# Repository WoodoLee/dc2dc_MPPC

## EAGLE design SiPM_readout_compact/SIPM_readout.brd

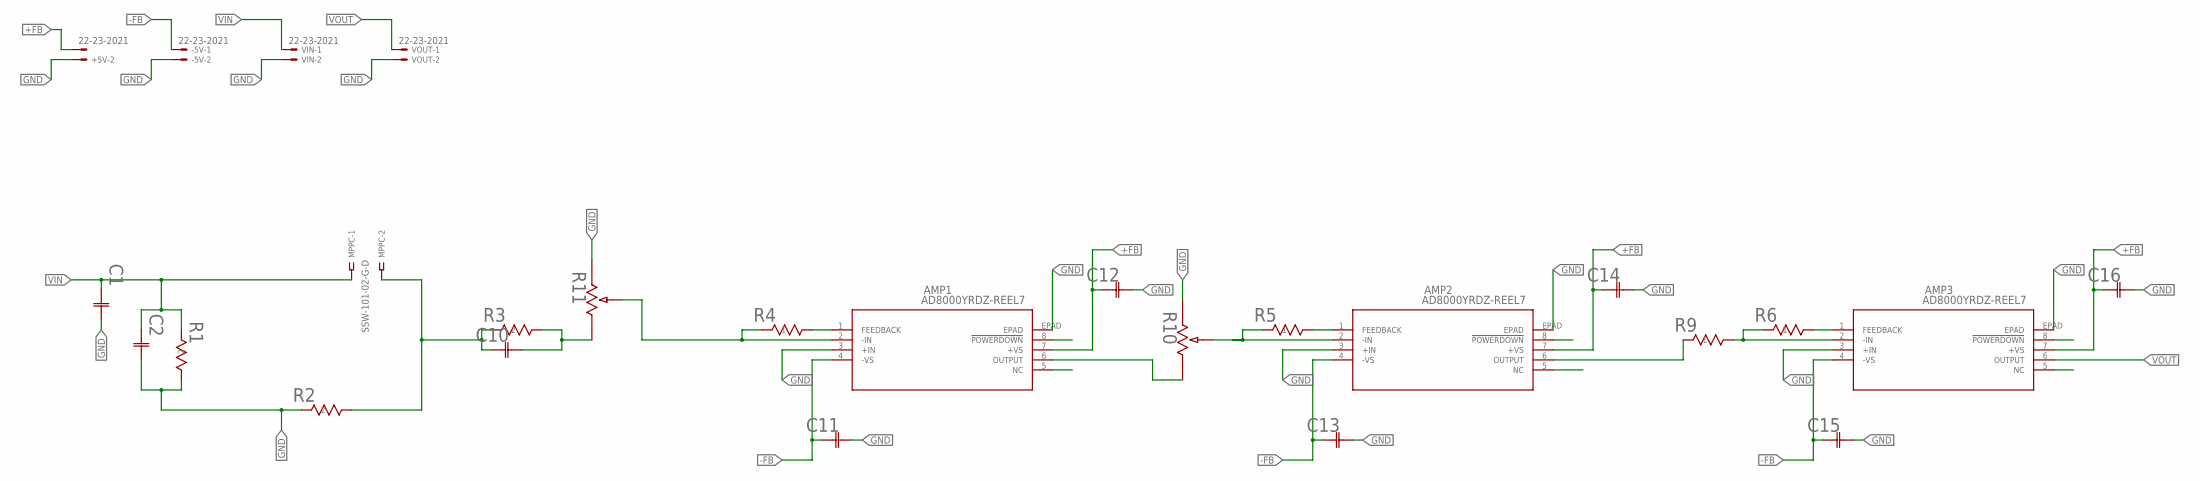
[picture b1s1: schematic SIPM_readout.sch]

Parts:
+5V: 22-23-2021
-5V: 22-23-2021
AMP1, AMP2, AMP3: AD8000YRDZ-REEL7; RD_8_1_ADI
C1: C3225X7S2A335M200ABCAP_3225_TDK-M; CAP_3225_TDK-M
C2: C3225X7R2A105K200AACAP_3225_TDK-M; CAP_3225_TDK-M
C10: CGA3E2C0G1H101J080AA; CAP_1608_TDK
C11, C12, C13, C14, C15, C16: CL10B104KB8NNNL; CAP_CL10_SAM
MPPC: SSW-101-02-G-D
R1: RC0603FR-072ML; RC0603N_YAG
R2, R3: RT0603BRD0710RL; RC0603N_YAG
R4, R5, R6, R9: ESR03EZPF1001; RES_R0603_ROM
R10, R11: 3214W-1-103E; POT_3214W
VIN: 22-23-2021
VOUT: 22-23-2021

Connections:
+FB: +5V.1, AMP1.7 (+VS), AMP2.7 (+VS), AMP3.7 (+VS), C12.1, C14.1, C16.1
-FB: -5V.1, AMP1.4 (-VS), AMP2.4 (-VS), AMP3.4 (-VS), C11.1, C13.1, C15.1
GND: +5V.2, -5V.2, AMP1.3 (+IN), AMP1.EPAD, AMP2.3 (+IN), AMP2.EPAD, AMP3.3 (+IN), AMP3.EPAD, C1.2, C2.2, C11.2, C12.2, C13.2, C14.2, C15.2, C16.2, R1.1, R2.2, R10.1, R11.1, VIN.2, VOUT.2
unnamed: AMP1.6 (OUTPUT), R10.3
unnamed: C10.1, MPPC.2, R2.1, R3.2
unnamed: C10.2, R3.1, R11.3
unnamed: AMP1.2 (-IN), R4.1, R11.2
unnamed: AMP1.1 (FEEDBACK), R4.2
unnamed: AMP2.1 (FEEDBACK), R5.2
unnamed: AMP2.2 (-IN), R5.1, R10.2
unnamed: AMP3.1 (FEEDBACK), R6.2
unnamed: AMP3.2 (-IN), R6.1, R9.2
unnamed: AMP2.6 (OUTPUT), R9.1
VIN: C1.1, C2.1, MPPC.1, R1.2, VIN.1
VOUT: AMP3.6 (OUTPUT), VOUT.1

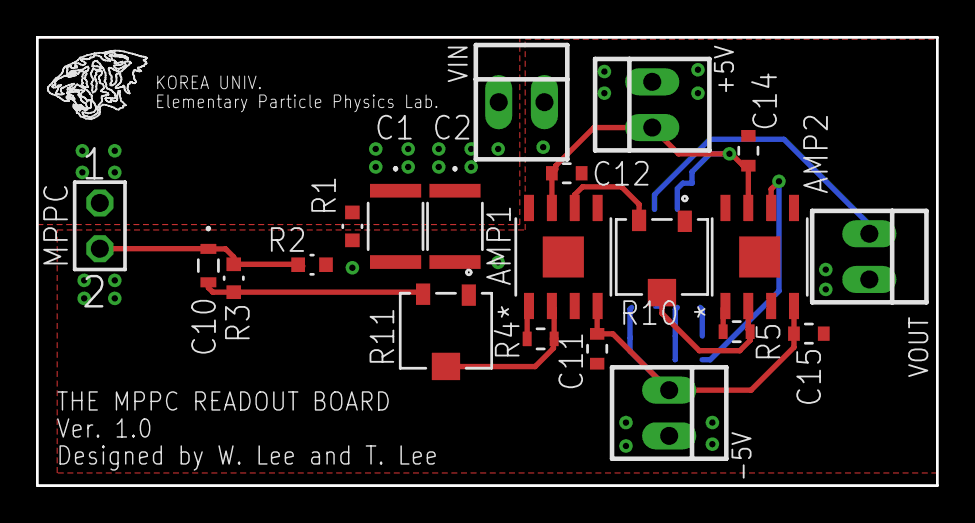
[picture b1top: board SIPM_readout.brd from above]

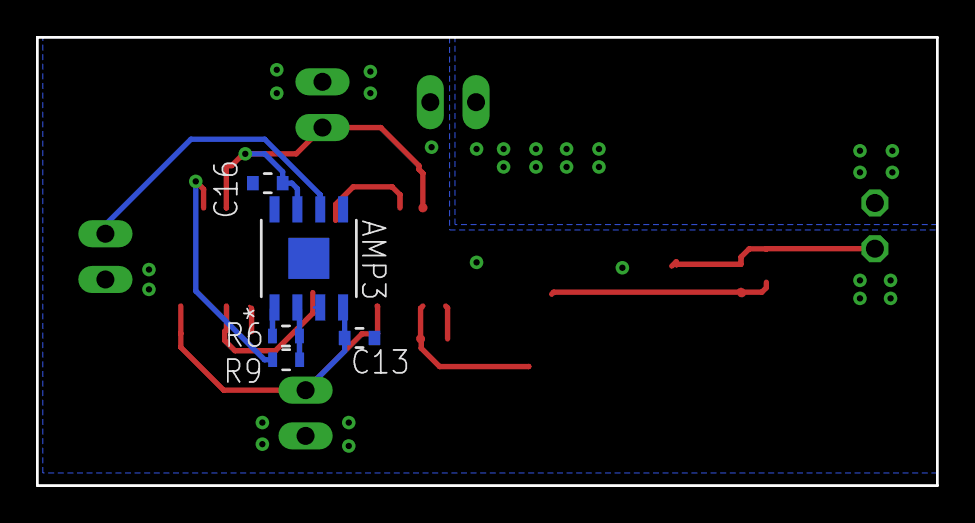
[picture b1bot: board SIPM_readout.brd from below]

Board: 2 copper layers, 50.0 x 24.9 mm, 26 parts (5 on the bottom side), 15 nets.

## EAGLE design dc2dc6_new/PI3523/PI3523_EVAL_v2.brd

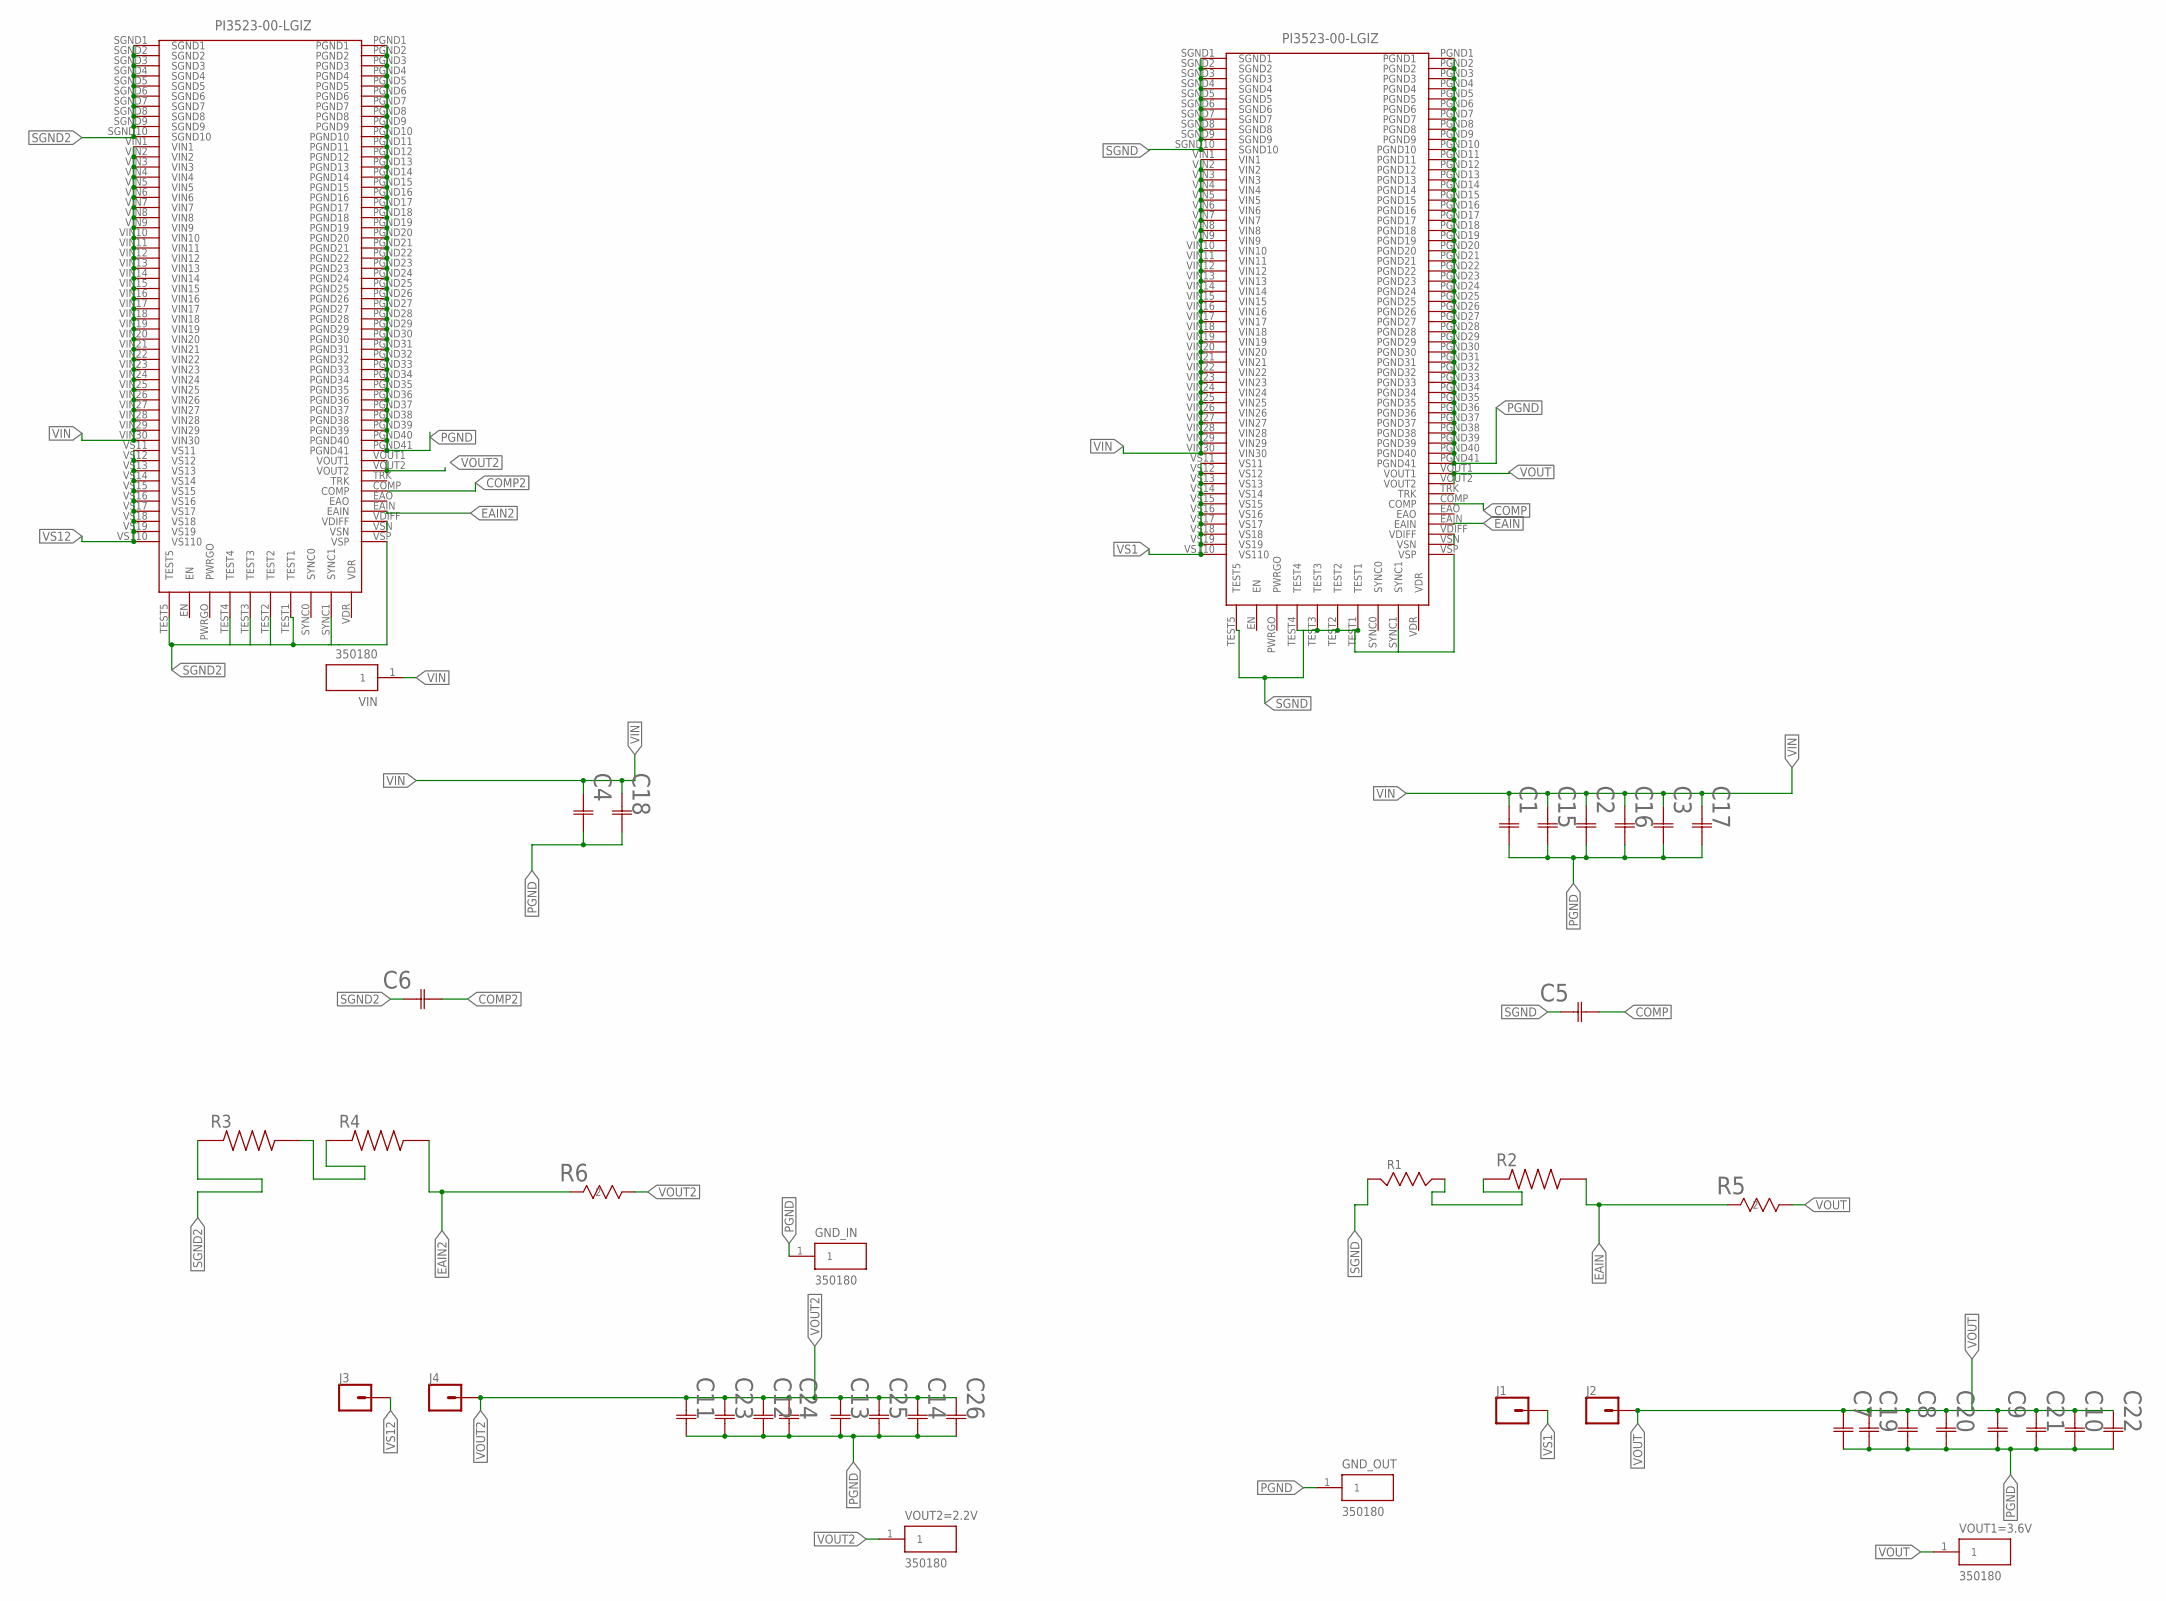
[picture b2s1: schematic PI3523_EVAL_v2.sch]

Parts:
C1, C2, C3, C4, C15, C16, C17, C18: GRM32ER72A225KA35L; G-32_MUR
C5, C6: C1608C0G2A472J080AC; CAP_C1608_TDK
C7, C8, C9, C10, C11, C12, C13, C14, C19, C20, C21, C22, C23, C24, C25, C26: GRM32EC80J107ME20L; G-32_MUR
GND_IN: 350180; TE_350180
GND_OUT: 350180; TE_350180
J1, J2, J3, J4: CONN_01; 1X01
R1: ERJ-3GEY0R00V; RESC1608X55
R2: ERA-3APB911V; RESC1608X55N
R3: ERJ-3BQJ3R6V; RESC1608X55N
R4: ERA-3AEB1961V; RESC1608X55N
R5, R6: RT0603BRE072K4L; RC0603N_YAG
U$1, U$2: PI3523-00-LGIZ
VIN: 350180; TE_350180
VOUT1=3.6V, VOUT2=2.2V: 350180; TE_350180

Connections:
COMP: C5.2, U$2.COMP
COMP2: C6.2, U$1.COMP
EAIN: R2.2, R5.2, U$2.EAIN
EAIN2: R4.2, R6.2, U$1.EAIN
unnamed: R3.2, R4.1
unnamed: U$2.VDIFF, U$2.VSN
unnamed: U$1.VDIFF, U$1.VSN
PGND: C1.2, C2.2, C3.2, C4.2, C7.2, C8.2, C9.2, C10.2, C11.2, C12.2, C13.2, C14.2, C15.2, C16.2, C17.2, C18.2, C19.2, C20.2, C21.2, C22.2, C23.2, C24.2, C25.2, C26.2, GND_IN.1, GND_OUT.1, U$1.PGND1, U$1.PGND2, U$1.PGND3, U$1.PGND4, U$1.PGND5, U$1.PGND6, U$1.PGND7, U$1.PGND8, U$1.PGND9, U$1.PGND10, U$1.PGND11, U$1.PGND12, U$1.PGND13, U$1.PGND14, U$1.PGND15, U$1.PGND16, U$1.PGND17, U$1.PGND18, U$1.PGND19, U$1.PGND20, U$1.PGND21, U$1.PGND22, U$1.PGND23, U$1.PGND24, U$1.PGND25, U$1.PGND26, U$1.PGND27, U$1.PGND28, U$1.PGND29, U$1.PGND30, U$1.PGND31, U$1.PGND32, U$1.PGND33, U$1.PGND34, U$1.PGND35, U$1.PGND36, U$1.PGND37, U$1.PGND38, U$1.PGND39, U$1.PGND40, U$1.PGND41, U$2.PGND1, U$2.PGND2, U$2.PGND3, U$2.PGND4, U$2.PGND5, U$2.PGND6, U$2.PGND7, U$2.PGND8, U$2.PGND9, U$2.PGND10, U$2.PGND11, U$2.PGND12, U$2.PGND13, U$2.PGND14, U$2.PGND15, U$2.PGND16, U$2.PGND17, U$2.PGND18, U$2.PGND19, U$2.PGND20, U$2.PGND21, U$2.PGND22, U$2.PGND23, U$2.PGND24, U$2.PGND25, U$2.PGND26, U$2.PGND27, U$2.PGND28, U$2.PGND29, U$2.PGND30, U$2.PGND31, U$2.PGND32, U$2.PGND33, U$2.PGND34, U$2.PGND35, U$2.PGND36, U$2.PGND37, U$2.PGND38, U$2.PGND39, U$2.PGND40, U$2.PGND41
R21_1: R1.2, R2.1
SGND: C5.1, R1.1, U$2.SGND1, U$2.SGND2, U$2.SGND3, U$2.SGND4, U$2.SGND5, U$2.SGND6, U$2.SGND7, U$2.SGND8, U$2.SGND9, U$2.SGND10, U$2.SYNC1, U$2.TEST1, U$2.TEST2, U$2.TEST3, U$2.TEST4, U$2.TEST5, U$2.VSP
SGND2: C6.1, R3.1, U$1.SGND1, U$1.SGND2, U$1.SGND3, U$1.SGND4, U$1.SGND5, U$1.SGND6, U$1.SGND7, U$1.SGND8, U$1.SGND9, U$1.SGND10, U$1.SYNC1, U$1.TEST1, U$1.TEST2, U$1.TEST3, U$1.TEST4, U$1.TEST5, U$1.VSP
VIN: C1.1, C2.1, C3.1, C4.1, C15.1, C16.1, C17.1, C18.1, U$1.VIN1, U$1.VIN2, U$1.VIN3, U$1.VIN4, U$1.VIN5, U$1.VIN6, U$1.VIN7, U$1.VIN8, U$1.VIN9, U$1.VIN10, U$1.VIN11, U$1.VIN12, U$1.VIN13, U$1.VIN14, U$1.VIN15, U$1.VIN16, U$1.VIN17, U$1.VIN18, U$1.VIN19, U$1.VIN20, U$1.VIN21, U$1.VIN22, U$1.VIN23, U$1.VIN24, U$1.VIN25, U$1.VIN26, U$1.VIN27, U$1.VIN28, U$1.VIN29, U$1.VIN30, U$2.VIN1, U$2.VIN2, U$2.VIN3, U$2.VIN4, U$2.VIN5, U$2.VIN6, U$2.VIN7, U$2.VIN8, U$2.VIN9, U$2.VIN10, U$2.VIN11, U$2.VIN12, U$2.VIN13, U$2.VIN14, U$2.VIN15, U$2.VIN16, U$2.VIN17, U$2.VIN18, U$2.VIN19, U$2.VIN20, U$2.VIN21, U$2.VIN22, U$2.VIN23, U$2.VIN24, U$2.VIN25, U$2.VIN26, U$2.VIN27, U$2.VIN28, U$2.VIN29, U$2.VIN30, VIN.1
VOUT: C7.1, C8.1, C9.1, C10.1, C19.1, C20.1, C21.1, C22.1, J2.1, R5.1, U$2.VOUT1, U$2.VOUT2, VOUT1=3.6V.1
VOUT2: C11.1, C12.1, C13.1, C14.1, C23.1, C24.1, C25.1, C26.1, J4.1, R6.1, U$1.VOUT1, U$1.VOUT2, VOUT2=2.2V.1
VS1: J1.1, U$2.VS11, U$2.VS12, U$2.VS13, U$2.VS14, U$2.VS15, U$2.VS16, U$2.VS17, U$2.VS18, U$2.VS19, U$2.VS110
VS12: J3.1, U$1.VS11, U$1.VS12, U$1.VS13, U$1.VS14, U$1.VS15, U$1.VS16, U$1.VS17, U$1.VS18, U$1.VS19, U$1.VS110

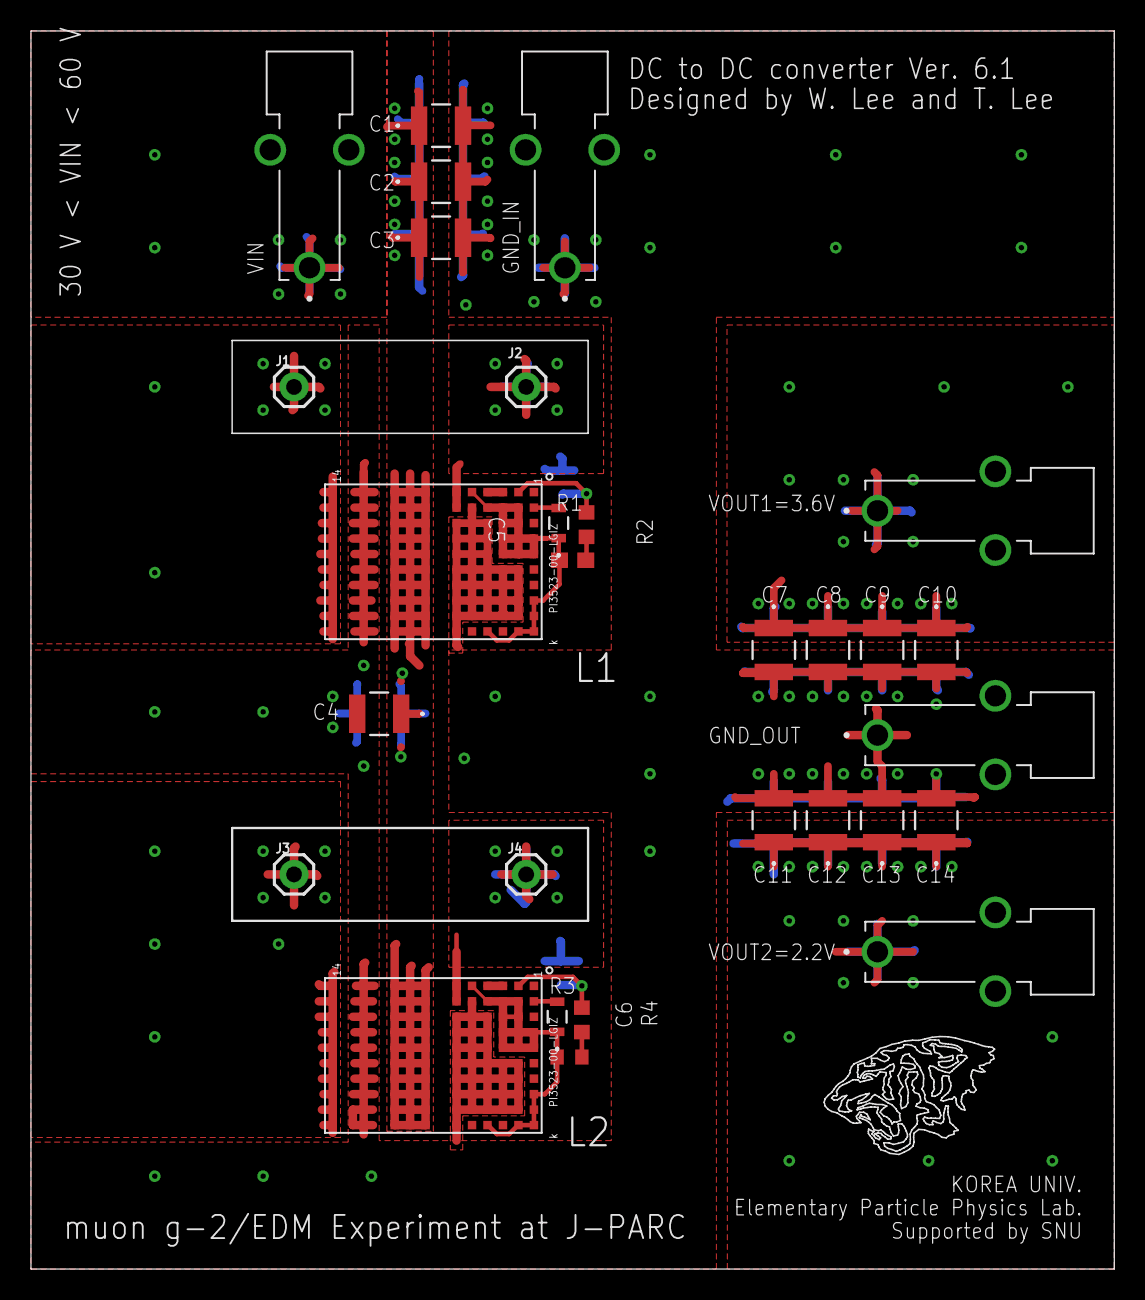
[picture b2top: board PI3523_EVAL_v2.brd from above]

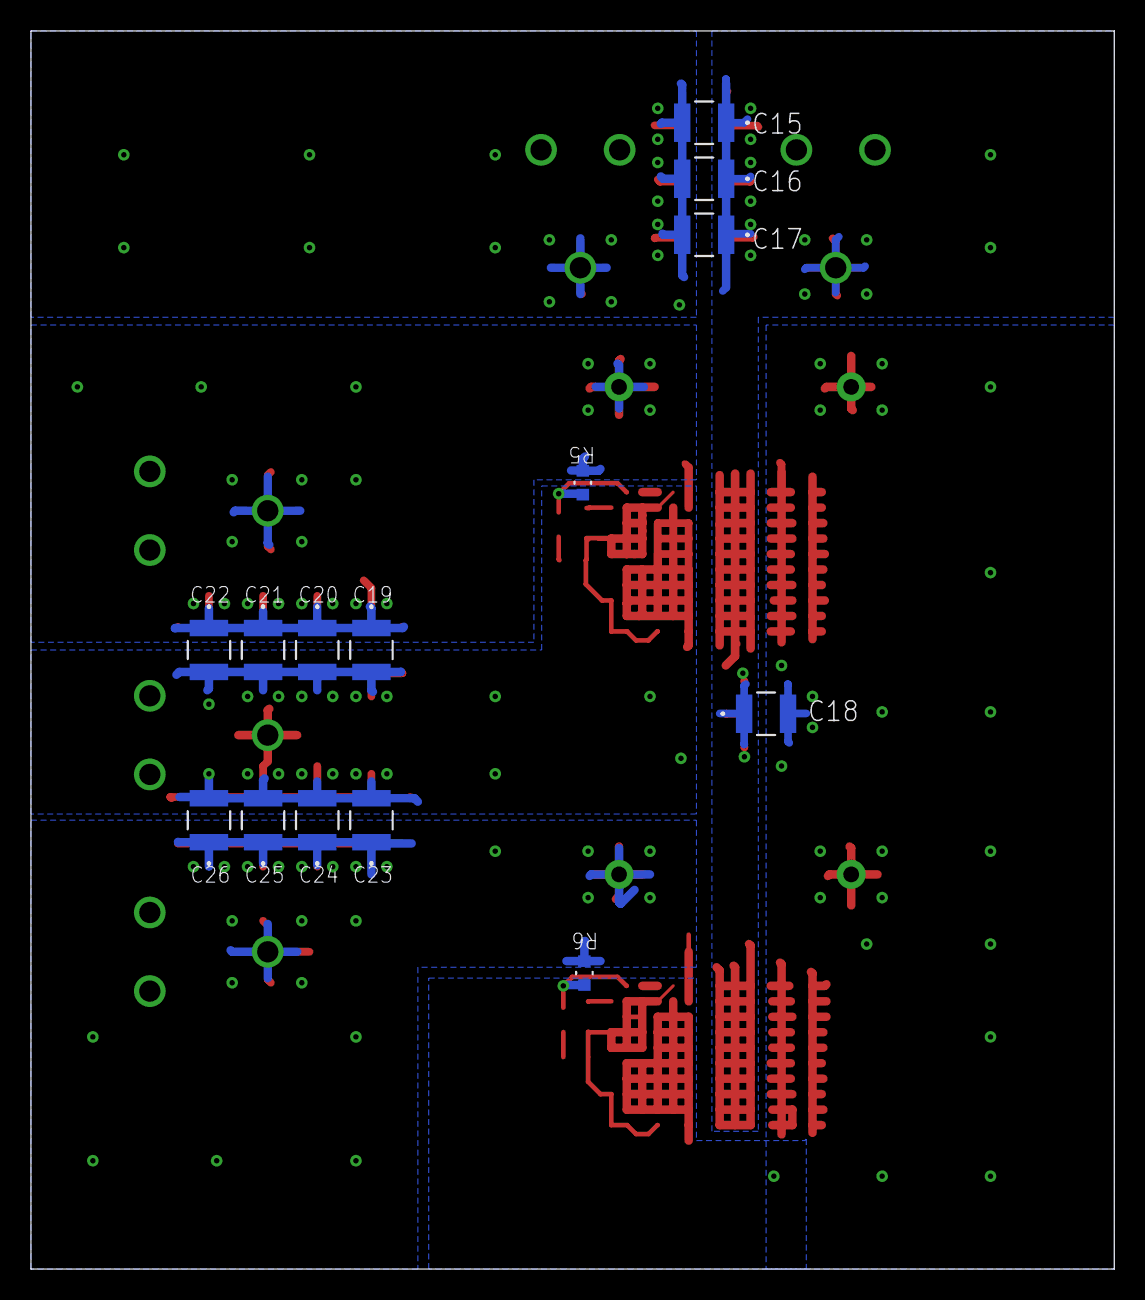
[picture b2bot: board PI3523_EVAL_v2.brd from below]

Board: 4 copper layers, 70.0 x 80.0 mm, 43 parts (14 on the bottom side), 16 nets.

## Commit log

2021-06-08 test
2021-06-08 MPPC
2021-06-17 compact
2021-06-17 final
2021-06-23 c1c2

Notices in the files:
parts and their libraries:
COPYRIGHT: Copyright (C) 2018 Accelerated Designs. All rights reserved
SparkFun-Connectors: Licensing: Creative Commons ShareAlike 4.0 International - https://creativecommons.org/licenses/by-sa/4.0
COPYRIGHT: Copyright (C) 2015 Accelerated Designs. All rights reserved
